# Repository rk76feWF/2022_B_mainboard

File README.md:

View this project on [CADLAB.io](https://cadlab.io/project/25282). 

# 2022_B_mainboard

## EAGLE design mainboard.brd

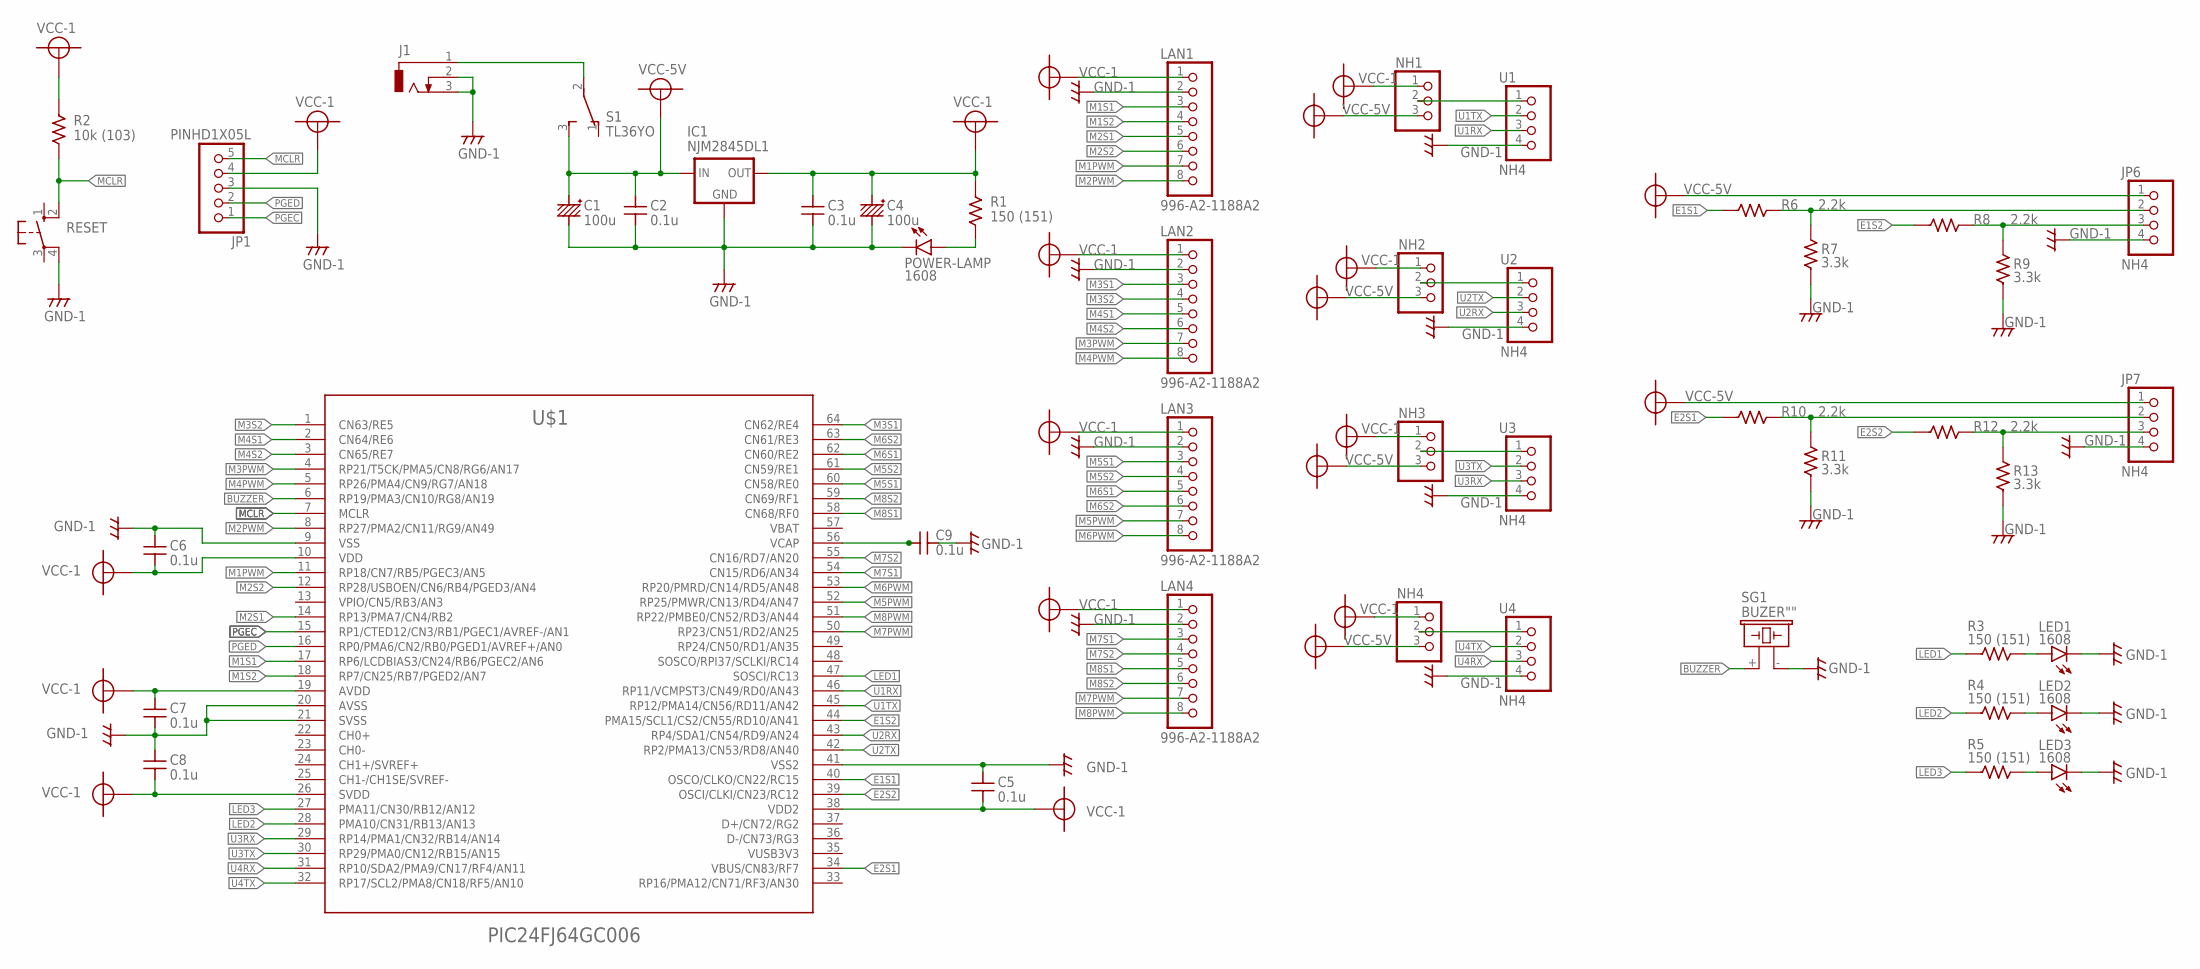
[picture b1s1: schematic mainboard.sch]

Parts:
C1, C4: 100u; CC:3
C2, C3, C5, C6, C7, C8, C9: 0.1u; C1608
IC1: NJM2845DL1; TO252
J1: DCJ0303
JP1: PINHD1X05L; 1X05L
JP6, JP7: NH4
LAN1, LAN2, LAN3, LAN4: 996-A2-1188A2
LED1, LED2, LED3: 1608; CHIP-LED0603
NH1, NH2, NH3, NH4: PINHD-1X3; 1X03
POWER-LAMP: 1608; CHIP-LED0603
R1, R3, R4, R5: 150 (151); C1608
R2: 10k (103); C1608
R6, R8, R10, R12: 2.2k; C1608
R7, R9, R11, R13: 3.3k; C1608
RESET: 10-XX; B3F-10XX
S1: TL36YO; TL3XYO
SG1: BUZER""; F/CM12P
U1, U2, U3, U4: NH4
U$1: PIC24FJ64GC006; TQFP64-10X10

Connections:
+5V: C1.+ (P$1+), C2.1, IC1.1 (IN), JP6.1, JP7.1, NH1.3, NH2.3, NH3.3, NH4.3, S1.3 (S)
BUZZER: SG1.+ (1), U$1.6 (RP19/PMA3/CN10/RG8/AN19)
E1S1: R6.2, U$1.40 (OSCO/CLKO/CN22/RC15)
E1S2: R8.2, U$1.44 (PMA15/SCL1/CS2/CN55/RD10/AN41)
E2S1: R10.2, U$1.34 (VBUS/CN83/RF7)
E2S2: R12.2, U$1.39 (OSCI/CLKI/CN23/RC12)
GND: C1.- (P$2-), C2.2, C3.2, C4.- (P$2-), C5.1, C6.1, C7.2, C8.1, C9.2, IC1.2 (GND), J1.2, J1.3, JP1.3, JP6.4, JP7.4, LAN1.2, LAN2.2, LAN3.2, LAN4.2, LED1.C, LED2.C, LED3.C, POWER-LAMP.C, R7.2, R9.2, R11.2, R13.2, RESET.4 (P1), SG1.- (2), U1.4, U2.4, U3.4, U4.4, U$1.9 (VSS), U$1.20 (AVSS), U$1.21 (SVSS), U$1.41 (VSS2)
LED1: R3.2, U$1.47 (SOSCI/RC13)
LED2: R4.2, U$1.28 (PMA10/CN31/RB13/AN13)
LED3: R5.2, U$1.27 (PMA11/CN30/RB12/AN12)
M1PWM: LAN1.7, U$1.11 (RP18/CN7/RB5/PGEC3/AN5)
M1S1: LAN1.3, U$1.17 (RP6/LCDBIAS3/CN24/RB6/PGEC2/AN6)
M1S2: LAN1.4, U$1.18 (RP7/CN25/RB7/PGED2/AN7)
M2PWM: LAN1.8, U$1.8 (RP27/PMA2/CN11/RG9/AN49)
M2S1: LAN1.5, U$1.14 (RP13/PMA7/CN4/RB2)
M2S2: LAN1.6, U$1.12 (RP28/USBOEN/CN6/RB4/PGED3/AN4)
M3PWM: LAN2.7, U$1.4 (RP21/T5CK/PMA5/CN8/RG6/AN17)
M3S1: LAN2.3, U$1.64 (CN62/RE4)
M3S2: LAN2.4, U$1.1 (CN63/RE5)
M4PWM: LAN2.8, U$1.5 (RP26/PMA4/CN9/RG7/AN18)
M4S1: LAN2.5, U$1.2 (CN64/RE6)
M4S2: LAN2.6, U$1.3 (CN65/RE7)
M5PWM: LAN3.7, U$1.52 (RP25/PMWR/CN13/RD4/AN47)
M5S1: LAN3.3, U$1.60 (CN58/RE0)
M5S2: LAN3.4, U$1.61 (CN59/RE1)
M6PWM: LAN3.8, U$1.53 (RP20/PMRD/CN14/RD5/AN48)
M6S1: LAN3.5, U$1.62 (CN60/RE2)
M6S2: LAN3.6, U$1.63 (CN61/RE3)
M7PWM: LAN4.7, U$1.50 (RP23/CN51/RD2/AN25)
M7S1: LAN4.3, U$1.54 (CN15/RD6/AN34)
M7S2: LAN4.4, U$1.55 (CN16/RD7/AN20)
M8PWM: LAN4.8, U$1.51 (RP22/PMBE0/CN52/RD3/AN44)
M8S1: LAN4.5, U$1.58 (CN68/RF0)
M8S2: LAN4.6, U$1.59 (CN69/RF1)
MCLR: JP1.5, R2.1, RESET.2 (S1), U$1.7 (MCLR)
unnamed: JP6.2, R6.1, R7.1
unnamed: J1.1, S1.2
unnamed: POWER-LAMP.A, R1.1
unnamed: LED1.A, R3.1
unnamed: LED2.A, R4.1
unnamed: LED3.A, R5.1
unnamed: JP6.3, R8.1, R9.1
unnamed: C9.1, U$1.56 (VCAP)
unnamed: JP7.2, R10.1, R11.1
unnamed: JP7.3, R12.1, R13.1
unnamed: NH1.2, U1.1
unnamed: NH2.2, U2.1
unnamed: NH3.2, U3.1
unnamed: NH4.2, U4.1
PGEC: JP1.1, U$1.15 (RP1/CTED12/CN3/RB1/PGEC1/AVREF-/AN1)
PGED: JP1.2, U$1.16 (RP0/PMA6/CN2/RB0/PGED1/AVREF+/AN0)
U1RX: U1.3, U$1.46 (RP11/VCMPST3/CN49/RD0/AN43)
U1TX: U1.2, U$1.45 (RP12/PMA14/CN56/RD11/AN42)
U2RX: U2.3, U$1.43 (RP4/SDA1/CN54/RD9/AN24)
U2TX: U2.2, U$1.42 (RP2/PMA13/CN53/RD8/AN40)
U3RX: U3.3, U$1.29 (RP14/PMA1/CN32/RB14/AN14)
U3TX: U3.2, U$1.30 (RP29/PMA0/CN12/RB15/AN15)
U4RX: U4.3, U$1.31 (RP10/SDA2/PMA9/CN17/RF4/AN11)
U4TX: U4.2, U$1.32 (RP17/SCL2/PMA8/CN18/RF5/AN10)
VCC-1: C3.1, C4.+ (P$1+), C5.2, C6.2, C7.1, C8.2, IC1.3 (OUT), JP1.4, LAN1.1, LAN2.1, LAN3.1, LAN4.1, NH1.1, NH2.1, NH3.1, NH4.1, R1.2, R2.2, U$1.10 (VDD), U$1.19 (AVDD), U$1.26 (SVDD), U$1.38 (VDD2)

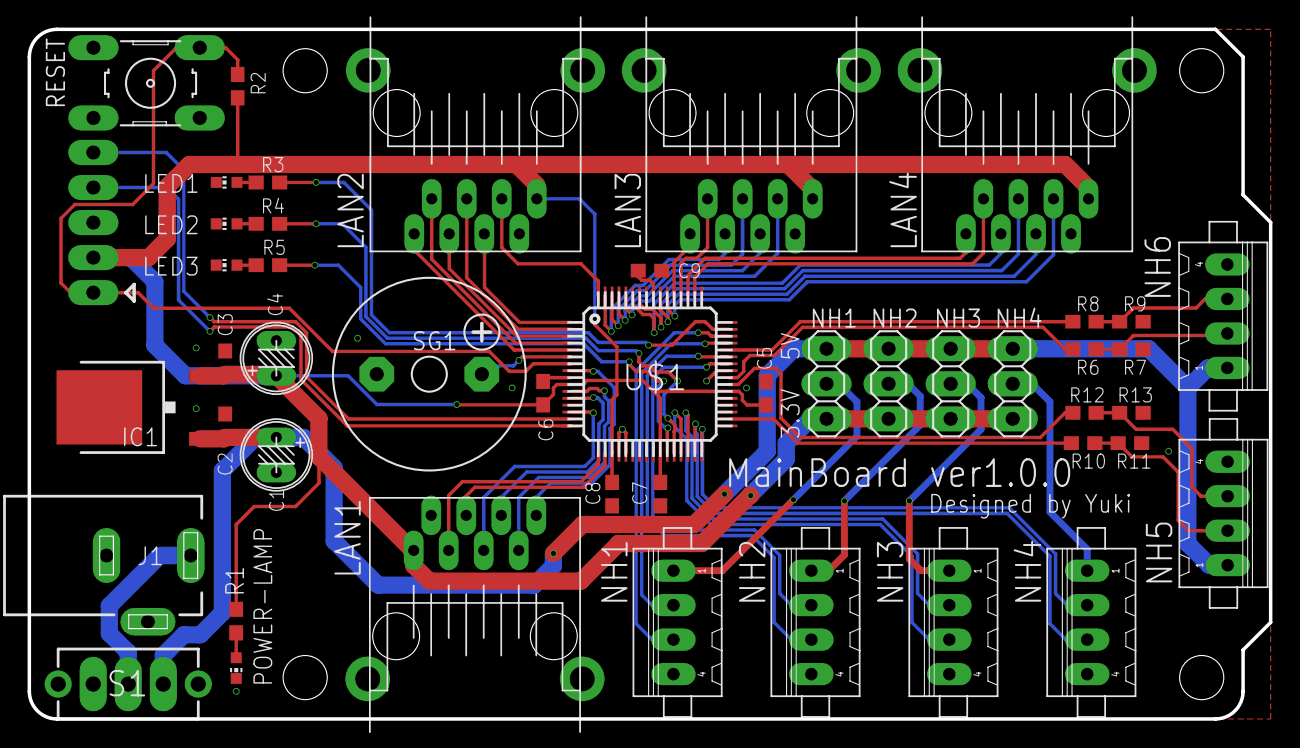
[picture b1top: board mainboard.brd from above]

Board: 2 copper layers, 90.0 x 50.0 mm, 47 parts (1 on the bottom side), 60 nets.

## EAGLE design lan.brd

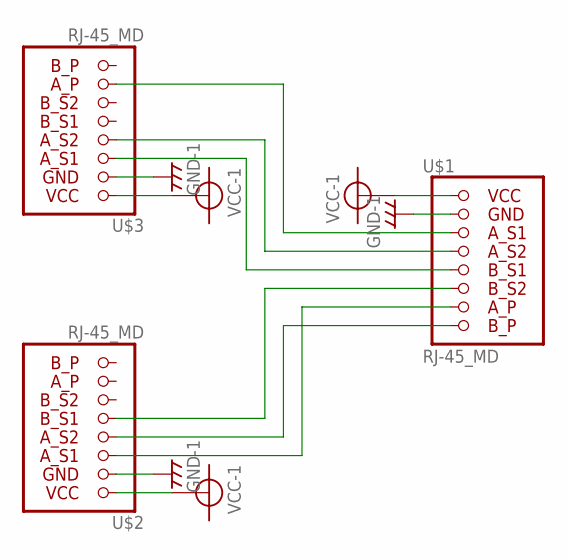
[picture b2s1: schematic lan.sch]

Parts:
U$1, U$2, U$3: RJ-45_MD; 996-A2-1188A2

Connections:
GND: U$1.2, U$2.2, U$3.2
unnamed: U$1.3, U$3.7
unnamed: U$1.4, U$3.4
unnamed: U$1.5, U$3.3
unnamed: U$1.8, U$2.4
unnamed: U$1.6, U$2.5
unnamed: U$1.7, U$2.3
VCC-1: U$1.1, U$2.1, U$3.1

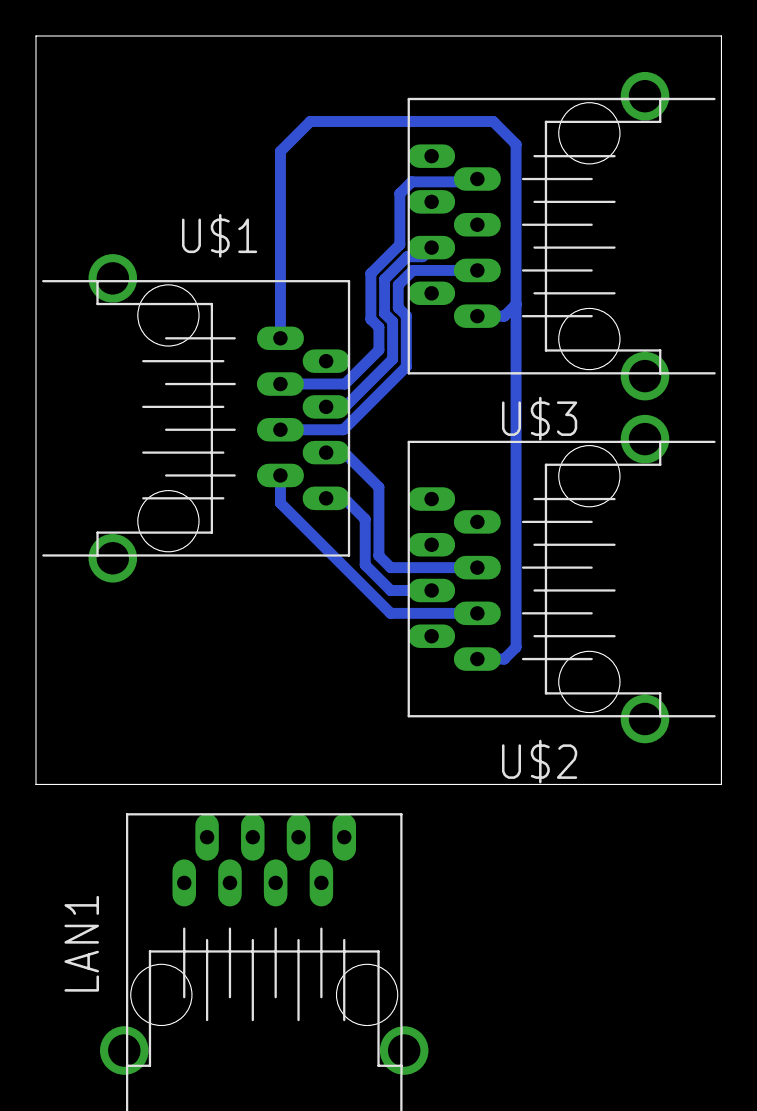
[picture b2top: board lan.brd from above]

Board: 2 copper layers, 38.1 x 41.6 mm, 4 parts (0 on the bottom side), 8 nets.

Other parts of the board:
LAN1: 996-A2-1188A2

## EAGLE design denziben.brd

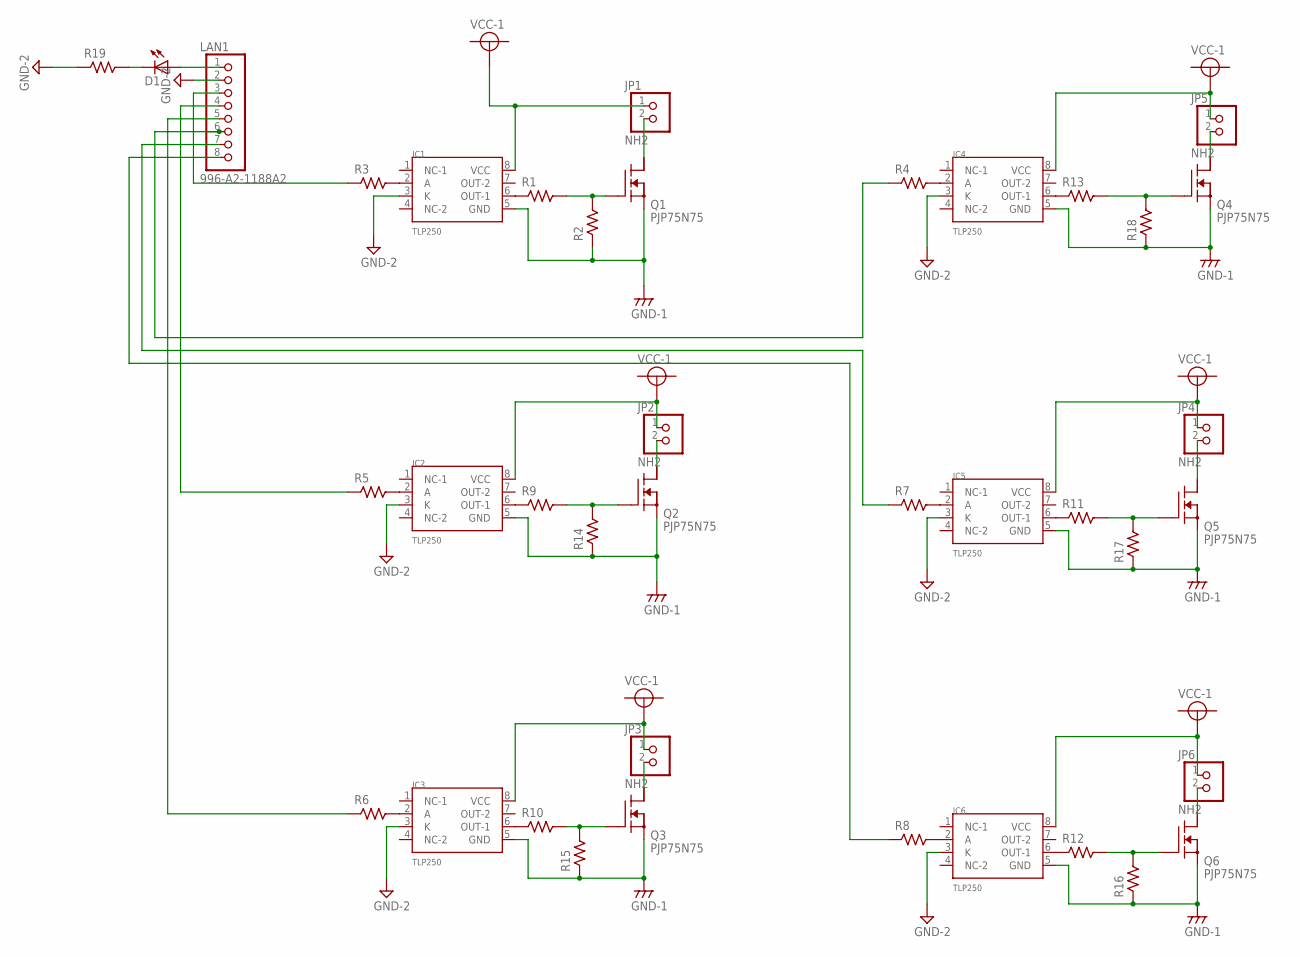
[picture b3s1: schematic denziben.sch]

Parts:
D1: LED""; LED5MM
IC1, IC2, IC3, IC4, IC5, IC6: TLP250; DIL8
JP1, JP2, JP3, JP4, JP5, JP6: NH2
LAN1: 996-A2-1188A2
Q1, Q2, Q3, Q4, Q5, Q6: PJP75N75; TO220
R1, R2, R3, R4, R5, R6, R7, R8, R9, R10, R11, R12, R13, R14, R15, R16, R17, R18, R19: R1/4W; R:1/4W

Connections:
GND: IC1.5 (GND), IC2.5 (GND), IC3.5 (GND), IC4.5 (GND), IC5.5 (GND), IC6.5 (GND), Q1.3 (NｃｈS), Q2.3 (NｃｈS), Q3.3 (NｃｈS), Q4.3 (NｃｈS), Q5.3 (NｃｈS), Q6.3 (NｃｈS), R2.P$1, R14.P$1, R15.P$1, R16.P$1, R17.P$1, R18.P$1
GND-2: IC1.3 (K), IC2.3 (K), IC3.3 (K), IC4.3 (K), IC5.3 (K), IC6.3 (K), LAN1.2, R19.P$1
unnamed: JP1.2, Q1.2 (NｃｈD)
unnamed: Q1.1 (Nｃｈ-G), R1.P$2, R2.P$2
unnamed: IC4.2 (A), R4.P$2
unnamed: IC1.6 (OUT-1), R1.P$1
unnamed: IC2.2 (A), R5.P$2
unnamed: IC3.2 (A), R6.P$2
unnamed: IC1.2 (A), R3.P$2
unnamed: IC6.2 (A), R8.P$2
unnamed: IC2.6 (OUT-1), R9.P$1
unnamed: IC3.6 (OUT-1), R10.P$1
unnamed: IC5.6 (OUT-1), R11.P$1
unnamed: IC6.6 (OUT-1), R12.P$1
unnamed: IC4.6 (OUT-1), R13.P$1
unnamed: Q3.1 (Nｃｈ-G), R10.P$2, R15.P$2
unnamed: Q6.1 (Nｃｈ-G), R12.P$2, R16.P$2
unnamed: Q5.1 (Nｃｈ-G), R11.P$2, R17.P$2
unnamed: Q4.1 (Nｃｈ-G), R13.P$2, R18.P$2
unnamed: Q2.1 (Nｃｈ-G), R9.P$2, R14.P$2
unnamed: LAN1.3, R3.P$1
unnamed: JP2.2, Q2.2 (NｃｈD)
unnamed: LAN1.4, R5.P$1
unnamed: LAN1.5, R6.P$1
unnamed: JP3.2, Q3.2 (NｃｈD)
unnamed: LAN1.6, R4.P$1
unnamed: LAN1.7, R7.P$1
unnamed: JP5.2, Q4.2 (NｃｈD)
unnamed: LAN1.8, R8.P$1
unnamed: IC5.2 (A), R7.P$2
unnamed: JP4.2, Q5.2 (NｃｈD)
unnamed: JP6.2, Q6.2 (NｃｈD)
unnamed: D1.A, LAN1.1
unnamed: D1.K (C), R19.P$2
VCC-1: IC1.8 (VCC), IC2.8 (VCC), IC3.8 (VCC), IC4.8 (VCC), IC5.8 (VCC), IC6.8 (VCC), JP1.1, JP2.1, JP3.1, JP4.1, JP5.1, JP6.1

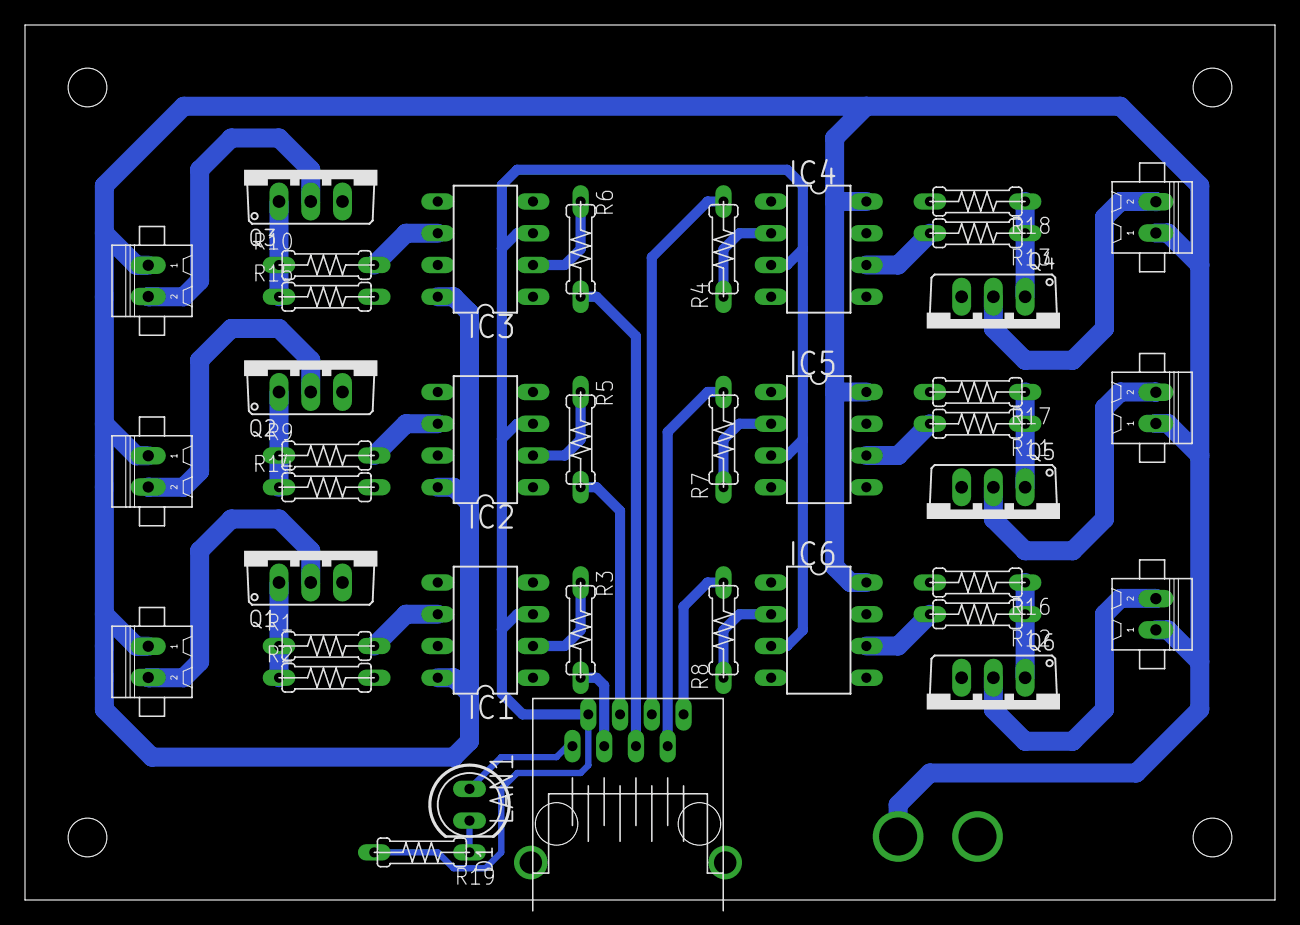
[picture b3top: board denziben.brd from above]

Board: 2 copper layers, 100.0 x 70.0 mm, 39 parts (0 on the bottom side), 35 nets.

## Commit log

2022-03-04 .gitignoreを追加
2022-03-04 CNCの設定を追加
2022-03-04 電磁弁制御用基板完成
2022-03-04 Backlink to CADLAB.io has been added.
2022-03-06 CNCの切削速度などを変更
2022-03-10 lan分岐用基板作成
2022-03-19 メイン基板が大体できた
2022-03-20 メイン基板LAN1の配線完了
2022-03-20 main基板配線完了
2022-03-22 main基板のデザインなどを変更
2022-03-22 main基板の微調整
2022-03-24 main基板のシルクの調整
2022-03-29 main基板のPICKITが刺さらない問題等を修正
2022-04-10 Clearanceのエラーが出ていた1か所を修正
2023-02-22 [Update] Update repository name
